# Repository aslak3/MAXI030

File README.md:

# MAXI030: a MC68030 based expandable computer

## Features as currently implemented

The specification for MAXI030, a [MC68030](https://www.nxp.com/docs/en/reference-manual/MC68030UM.pdf) based computer, is as follows:

* A core "glue" that is wired to [master](https://en.wikipedia.org/wiki/Bus_mastering) the 32 bit busses
* Glue is provided by an [EPF10K130EQC240-1](https://www.micro-semiconductor.com/datasheet/12-EPF10K100EFC256-2AA.pdf) FPGA
* A 68030 coupled with a [68882](https://www.nxp.com/docs/en/data-sheet/BR509.pdf)
* 512K x 16 flashes in the form of 2 x [SST39SF040](http://ww1.microchip.com/downloads/en/DeviceDoc/20005022C.pdf) in PLCC32
* 2 x [72 pin SIMM](https://en.wikipedia.org/wiki/SIMM#72-pin_SIMMs) slots with a controller implemented in the FPGA
* A [SC26C94](https://pdf.dzsc.com/6C9/SC26C94.pdf) QUART with the following arrangements of the four serial ports:
  * Two on RJ45 at RS-232 levels following the standard Cisco pinnout
  * One for [my Amiga 600 keyboard](https://www.aslak.net/index.php/amiga-600-avr-based-keyboard-controller/) on an RJ11
  * And a TTL header for debug and the bring-up
* Onboard 10Mbit/s Ethernet using a [RTL8019AS](http://www.ethernut.de/pdf/8019asds.pdf)
* A [PS/2](https://en.wikipedia.org/wiki/PS/2_port) port for keyboard and mouse using a splitter cable
* Four 16 bit wide by 16 MByte deep expansion slots compatible with cards like my [video card](https://www.aslak.net/index.php/2021/07/08/the-design-of-a-video-and-sound-card-for-midi020/) which was implemented for my earlier MC68020 board
* I2C bus with:
  * [DS13057](https://datasheets.maximintegrated.com/en/ds/DS1307.pdf) RTC
  * [LM75A](https://www.nxp.com/docs/en/data-sheet/LM75A.pdf) temperature sensor
  * [PCA9544APW](https://www.nxp.com/docs/en/data-sheet/PCA9544A.pdf) four way expansion slot bus multiplexer allowing expansion cards to attach to the I2C bus
* [IDE](https://en.wikipedia.org/wiki/Parallel_ATA) with DMA signals routed to the FPGA, though they are currently not utilised
* A [P7805-2000-S](https://www.mouser.co.uk/datasheet/2/670/p78_2000_s-1729053.pdf) 2A 5V potted switching regulator attached to a barrel jack

A [schematic](MAXI030.pdf) is included here, along with the [KiCAD](https://www.kicad.org) data files. Note that schematic symbols are included in the library cache. Whilst these boards were designed with KiCAD 4, the files in this repository are all KiCAD 6 format.

## PCB design

The PCB is a 4 layer board. The requirements to make the board are quite heavy; 6 mil traces are used, with 6.5 mil clearances between them. 3 traces pass between 100mil spaced pins in multiple places. My boards were manufactured by [JLCPCB](https://www.jlcpcb.com) with no issues.

## Glue logic core

A major feature of this board is the EPF10K130EQC240 FPGA. This component is part of Altera's [Flex 10KE](https://www.micro-semiconductor.com/datasheet/12-EPF10K100EFC256-2AA.pdf) family, which is a 3.3V/2.5V part descended from the [Flex 10K](https://www.dexsilicium.com/altera_flex_epf10k.pdf) line of 5V parts. These FPGAs are unfortunately obsolete, and difficult to get hold of; I sourced mine from [UTSource](https://www.utsource.net).

The board uses mixed 3.3V and 5V signaling. The Flex 10KE series is "special" in that it is fully 5V tolerant without an inline resistor, unlike later Altera parts such as the early Cylcones which are 5V tolerant but need an inline resistor. The Flex 10KE also have outputs compatible with 5V TTL levels. My previous projects have made heavy use of the 5V Flex 10K parts, but I have found that as the board frequency has increased, these FPGAs have reached their limit. Consequently this board switched to the Flex 10KE, despite the complexities inherent in a mixed signal level board.

Beside getting hold of the actual part a challenge facing anyone building this board is obtaining a compatible Altera Quartus version since Intel have, in their wisdom, removed from their site the 9.0sp2 version; the last that supported the Flex 10K(E) series. It can still be obtained if you know where to look, however.

Another small annoyance, related to the FPGA side of the board, is that two EPC2 configuration flashes are needed since this is a large, for the time, FPGA.

I have implemented the following functionality, all in VHDL:

* Core glue, address decoding etc
* A basic DRAM controller for one of the SIMM slots
* Buzzer and LED driver
* Simplistic interrupt routing (autovectored only for now)
* An I2C master to operate the RTC and temperature sensor
* A PS/2 controller for both PS/2 connections
* An SPI output channel, and bi-directional UART, both for debugging

The code for this functionality resides in the [MAXI030Core directory](MAXI030Core), where a more detailed description of the files used can be found.

As this is FPGA hardware, many other things could be implemented. In particular, the FPGA is wired to the full 32 bits of address and data, so a bus-mastering DMA controller could be constructed. This could be used for disk transfers, amongst other things, which would greatly speed up these operations. The interrupt handling is also basic at present, and vectored interrupts should probably be used.

It's worth pointing out, for completeness, that since the FPGA is attached to a 32 bit wide by 4GB address space it would theoretically be possible to use this board to replace the 68030 with some other custom softcore processor running inside the FPGA, with the 68030 disabled or simply not present. Perhaps a more interesting opportunity would be to implement a custom 68020+ style co-processor.

## Expansion Cards

The following three cards have been created:

1. [TestSRAM](ExpansionCards/TestSRAM/) - This is card is only really useful for the bringup. It has two 512KB SRAMs attached, along with pin headers attached to he expansion bus. It allows the system to be used without having a SIMM attached (and working).
2. [Printer+Sticks](ExpansionCards/Printer%2BSticks/) - This is a fairly simple card featuring a [MC68230](http://www.ceipsa.com/datasheet/MC68230.pdf) and some latches. The board does not feature a DB25 connector, instead the printer must be attached through a "standard" 2x13 PC style adapter. The latches are attached to DB9 Atari-style joystick ports.
3. [Video+Sound](ExpansionCards/Video%2BSound/) - The most interesting card by far; this a VGA card implemented with a Cyclone II FPGA and some fast 16 bit SRAM to hold the video framebuffer. Also featured is an I2S DAC.

The TestxSRAM card (such as it is) has been shown to be error-free. The Printer+Joystick card has been exercised by attaching an old 9 pin dot matrix printer and printing text, though this was with the earlier MIDI020 68020 board. The Video+Sound board has been attached to MAXI030 and, though it has a few teaming troubles, it appears to work well. The sound portion of that card has not been explored at all however.

More documentation on these cards will be forthcoming. For now, each expansion card directory contains the schematic and PCB files in KiCAD format, plus a PDF of the schematic, the BOM, and the rendered gerbers used to produce the cards.

## Machine-code monitor

Over the years I've extended my monitor to run on each 68K based board as I've produced them. The monitor is basic, but serviceable. It is in no way designed for software development; it's main purpose is to exercise the hardware. It has low-level (memory/IO operations) and high level functionality:

* IDE identify, read and write sectors
* PS/2 reading/writing
* I2C reading/writing
* And others

It is also used to start the Linux kernel.

The monitor source is held in its [own repository](https://www.github.com/aslak3/m68k-monitor).

## Linux

A Linux port has been started and seems to work quite well. The following hardware has been shown to work, by making very small changes to existing drivers or creating new ones:

* /dev/ttySC{0,1} UART ports - these map to Port A and Port B on the board
* IDE - though neither interrupt mode or DMA is currently supported so it is rather slow
* Ethernet - works well, though the transfers are on an 8 bit port
* RTC and temperature sensor - an I2C bus driver has been produced which can talk to these peripherals
* PS/2 - the driver implemented supports both ports
* Framebuffer - a very slow and Work in Progress driver for the video card I've built

With a 32MHz can installed, a modern Linux kernel will boot in about 2.5 minutes. But see the Gotchas section below.

A [fork of the Linux kernel](https://www.github.com/aslak3/linux.git) from early 2022 has work done at the head of the lm/maxi030 branch with the changes I've made.

The userland I'm currently using is based on a very old Debian build, even though the kernel is almost the latest, since running the latest 68k Debian packages results in a very slow system. This is another thing to investigate.

A script, which is a total hack, for generating an directory tree of Debian Linux is available in the [linux](linux) directory. This script can generate both sid (current) and sarge (old) Debian images. It must be edited before use to set the DNS resolver, interface addressing, passwords, custom packages and other things. It makes use of [multistrap](https://wiki.debian.org/Multistrap) and [QEUMU's 68K support](https://wiki.qemu.org/Documentation/Platforms/m68k) to do its thing.

As it currently stands, the Linux system is useable across the UART (via a login getty), and via the network. Both SSH and telnet are available, SSH being extremely slow as predicted. Console access, using the PS/2 port and my bitmap video card, is very much a work in progress, though I did have X running (very, very slowly) at one point.

The general process to get Linux running on MAXI030 is as follows, assuming the board is up and running with the monitor available via a UART port:

1. At present the MAC address of the Linux host, which will supply the image, is hardcoded into the monitor program in ne2k.c in the ne2k_transmit subroutine; change it to your PCs MAC address. Note that the MAXI030 MAC address is hardcoded to 11:22:33:44:55:66
2. Build a suitably patched kernel and convert it to a raw image
3. Modify the eth-sender program as required, at a minimum the device name for the connected ethernet interface is hardcoded
4. Run up the eth-sender program (it requires root), the kernel should be available in the same directory and called vmlinux.bin
5. Partition a Compact Flash: two partitions using MBR, partition 1 for swap and 2 for the rootfs in ext3 (ext4 will work with a newer Debian userland)
6. Modify the make-multistrap script as required
7. Create the Debian directory structure and copy it into partition two on the Compact Flash
8. Create a swap partition (mkswap) on partition one
9. Plug in the Compact Flash and turn on MAXI030
10. Transfer the kernel to MAXI030 with the linuxdl command
11. Run the kernel with a monitor command like: linuxrun "console=ttySC0,38400 root=/dev/sda2"
12. Wait for kernel to boot
13. Login via the getty, test the network etc

## Issues

The big issue I'm currently working on is board speed. With all the functionality enabled in the FPGA design, I'm currently not able to run the board at the maximum speed of the 68030 I have installed, 40MHz. Insteaed I must settle for running the board at 32MHz. In particular adding the FIFOs on the PS/2 controller results in an inoperable system at 40MHz. The FIFOs seem to be required when running in Linux since the kernel disables interrupts in some situations, which results in data loss.

The board also has a few very minor problems:

* The switching regulator footprint matches the 1A [SR10S05](https://www.xppower.com/portals/0/pdfs/SF_SR.pdf) and similar; the original 2A part fits but must hang off the board since its pinout is reversed. In use and with the video card inserted and a single SIMM attached I've rarely seen the current draw pass 500mA so I think a 1A regulator will be fine
* The silk screen labels for UART Port A and Port B are the wrong way around
* The labels for Enable/Disable on the MMU/cache jumpers are also backwards

## Blog

The best place to learn about this board is undoubtably [my blog](https://www.aslak.net/index.php/category/68k/), including these posts:

* [The design of MAXI030](https://www.aslak.net/index.php/2021/10/02/the-design-of-a-68030-based-expandable-computer/)
* [Porting Linux to the MAXI030](https://www.aslak.net/index.php/2022/01/11/porting-linux-to-the-68030-based-maxi030/)

I've also made a [short YouTube video](https://www.youtube.com/watch?v=WL3ttsiriho), which discusses the board and demos the Linux port.

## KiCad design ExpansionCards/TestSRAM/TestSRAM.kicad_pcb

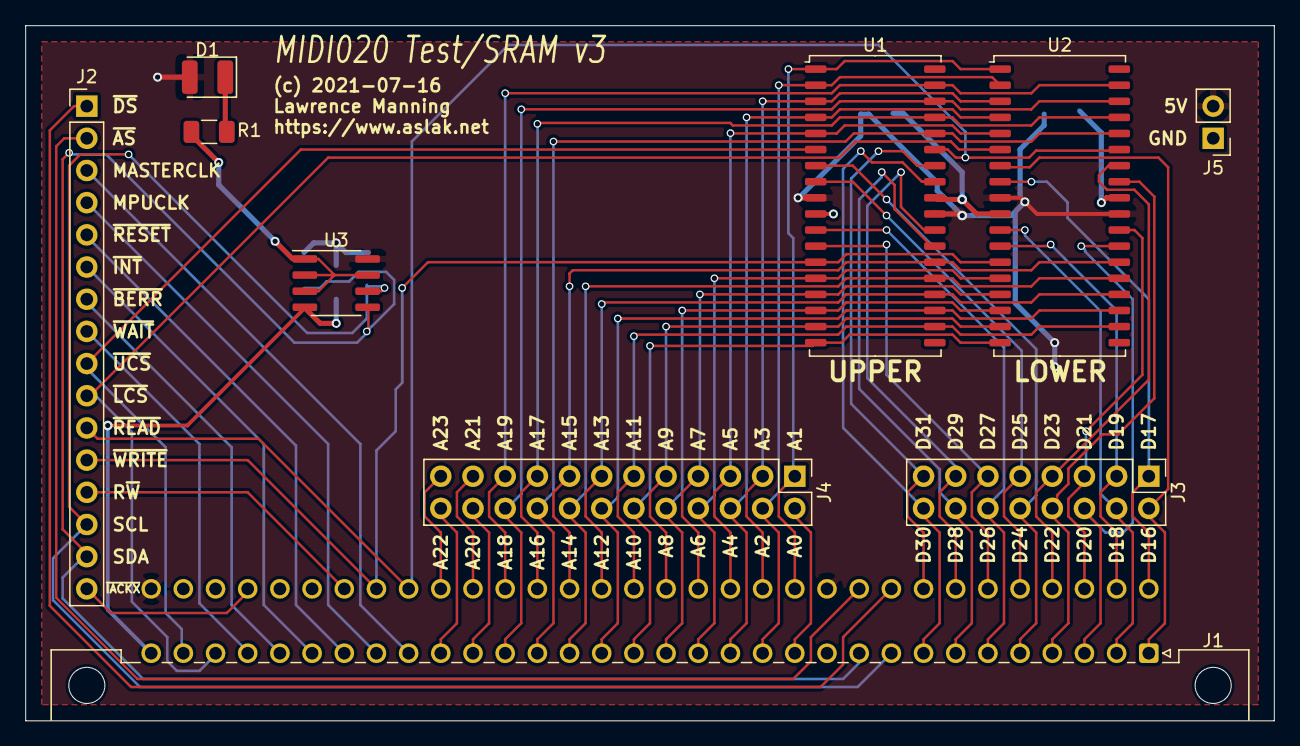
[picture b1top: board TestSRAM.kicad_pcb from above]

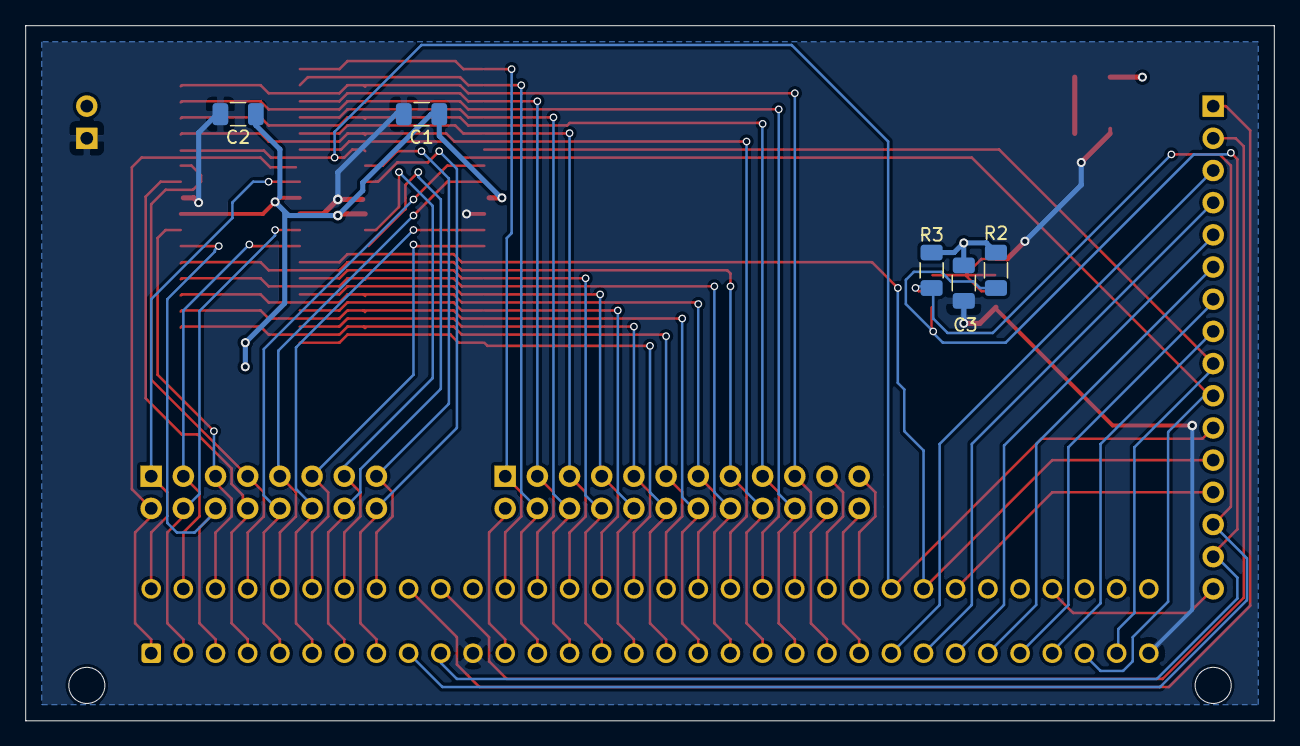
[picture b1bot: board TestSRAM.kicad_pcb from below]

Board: 2 copper layers, 98.6 x 54.9 mm, 15 parts (5 on the bottom side), 59 nets.

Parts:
C1, C2, C3: 0.1u; C_1206_3216Metric
D1: LED; LED_1210_3225Metric
J1: DIN_41612_3x32_MIDI020_CARD; DIN41612_C_2x32_Male_Horizontal_THT
J2: Conn_01x16; PinHeader_1x16_P2.54mm_Vertical
J3: Conn_02x08_Odd_Even; PinHeader_2x08_P2.54mm_Vertical
J4: Conn_02x12_Odd_Even; PinHeader_2x12_P2.54mm_Vertical
J5: Conn_01x02; PinHeader_1x02_P2.54mm_Vertical
R1: 1K; R_1206_3216Metric
R2, R3: 4.7K; R_1206_3216Metric
U1, U2: IS61C5128AL-10KLI; SOJ-36_10.16x23.49mm_P1.27mm
U3: AT24CS64-SSHM; SOIC-8_3.9x4.9mm_P1.27mm

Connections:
+5VD: C1.1, C2.1, C3.1, D1.2, J1.c11, J1.c32, J5.2, R2.1, R3.1, U1.9, U1.27, U2.9, U2.27, U3.8
/A0: J1.a12, J4.2
/A1: J1.c12, J4.1, U1.1, U2.1
/A2: J1.a13, J4.4, U1.2, U2.2
/A3: J1.c13, J4.3, U1.3, U2.3
/A4: J1.a14, J4.6, U1.4, U2.4
/A5: J1.c14, J4.5, U1.5, U2.5
/A6: J1.a15, J4.8, U1.14, U2.14
/A7: J1.c15, J4.7, U1.15, U2.15
/A8: J1.a16, J4.10, U1.16, U2.16
/A9: J1.c16, J4.9, U1.17, U2.17
/A10: J1.a17, J4.12, U1.18, U2.18
/A11: J1.c17, J4.11, U1.20, U2.20
/A12: J1.a18, J4.14, U1.21, U2.21
/A13: J1.c18, J4.13, U1.22, U2.22
/A14: J1.a19, J4.16, U1.23, U2.23
/A15: J1.c19, J4.15, U1.24, U2.24
/A16: J1.a20, J4.18, U1.32, U2.32
/A17: J1.c20, J4.17, U1.33, U2.33
/A18: J1.a21, J4.20, U1.34, U2.34
/A19: J1.c21, J4.19, U1.35, U2.35
/A20: J1.a22, J4.22
/A21: J1.c22, J4.21
/A22: J1.a23, J4.24
/A23: J1.c23, J4.23
/D16: J1.a1, J3.2, U2.7
/D17: J1.c1, J3.1, U2.8
/D18: J1.a2, J3.4, U2.11
/D19: J1.c2, J3.3, U2.12
/D20: J1.a3, J3.6, U2.25
/D21: J1.c3, J3.5, U2.26
/D22: J1.a4, J3.8, U2.29
/D23: J1.c4, J3.7, U2.30
/D24: J1.a5, J3.10, U1.7
/D25: J1.c5, J3.9, U1.8
/D26: J1.a6, J3.12, U1.11
/D27: J1.c6, J3.11, U1.12
/D28: J1.a7, J3.14, U1.25
/D29: J1.c7, J3.13, U1.26
/D30: J1.a8, J3.16, U1.29
/D31: J1.c8, J3.15, U1.30
GNDD: C1.2, C2.2, C3.2, J1.a11, J1.a32, J5.1, R1.1, U1.10, U1.28, U2.10, U2.28, U3.1, U3.2, U3.3, U3.4, U3.7
MASTERCLK: J1.a24, J2.3
MPUCLK: J1.a25, J2.4
unnamed: D1.1, R1.2
R~W: J1.c26, J2.13
SCL: J1.a9, J2.14, R3.2, U3.6
SDA: J1.a10, J2.15, R2.2, U3.5
~AS: J1.c10, J2.2
~BERR: J1.a28, J2.7
~DS: J1.c9, J2.1
~IACKX: J1.c29, J2.16
~INT: J1.a27, J2.6
~LCS: J1.a30, J2.10, U2.6
~READ: J1.c24, J2.11, U1.31, U2.31
~RESET: J1.a26, J2.5
~UCS: J1.a31, J2.9, U1.6
~WAIT: J1.a29, J2.8
~WRITE: J1.c25, J2.12, U1.13, U2.13

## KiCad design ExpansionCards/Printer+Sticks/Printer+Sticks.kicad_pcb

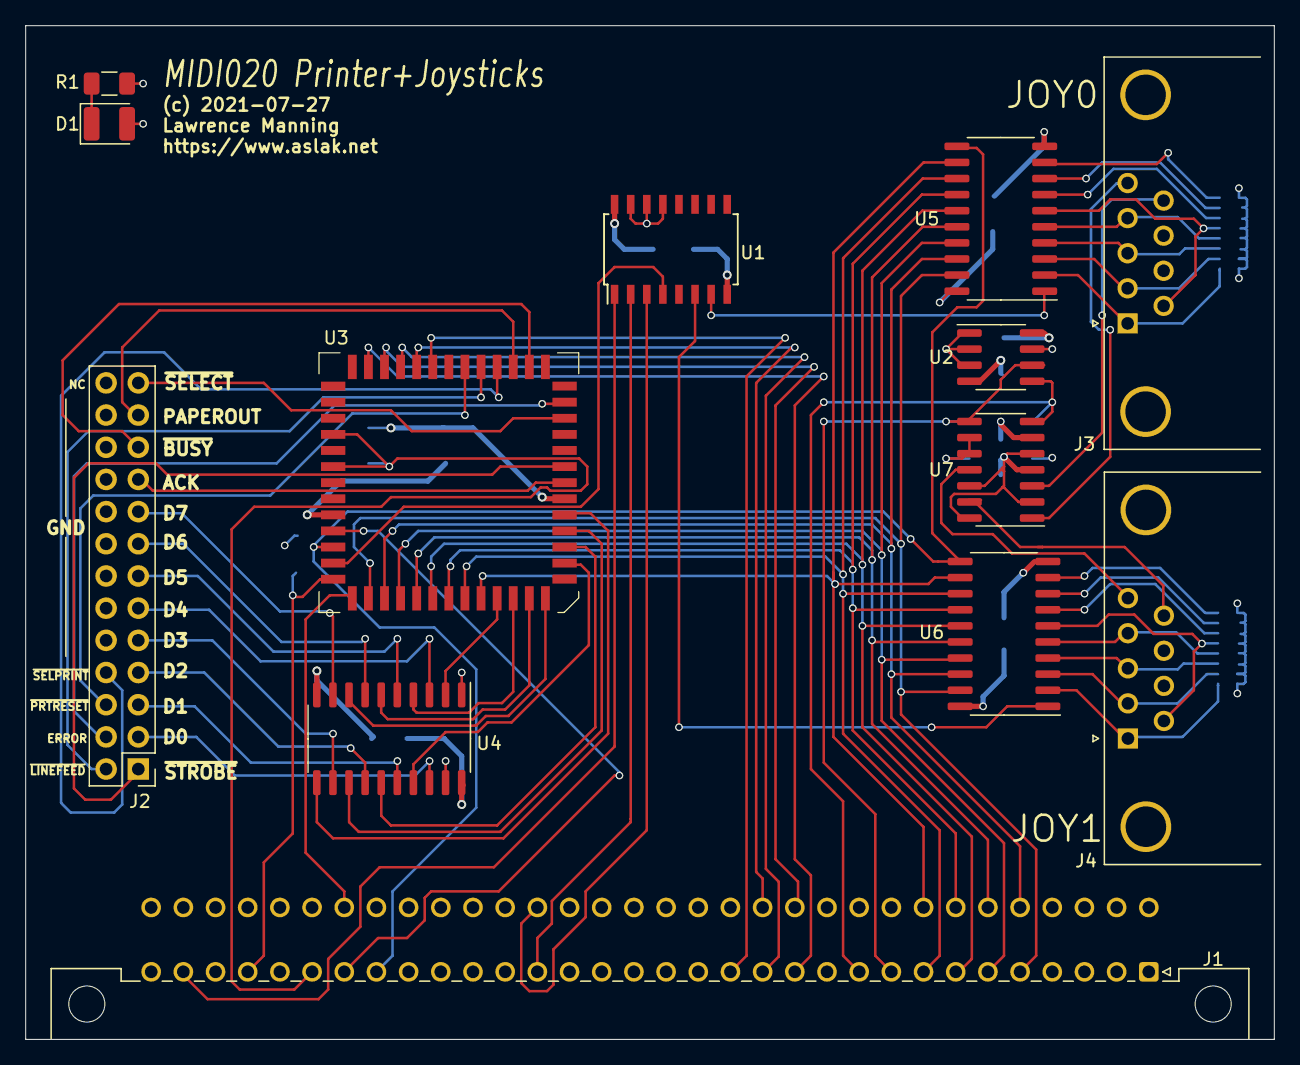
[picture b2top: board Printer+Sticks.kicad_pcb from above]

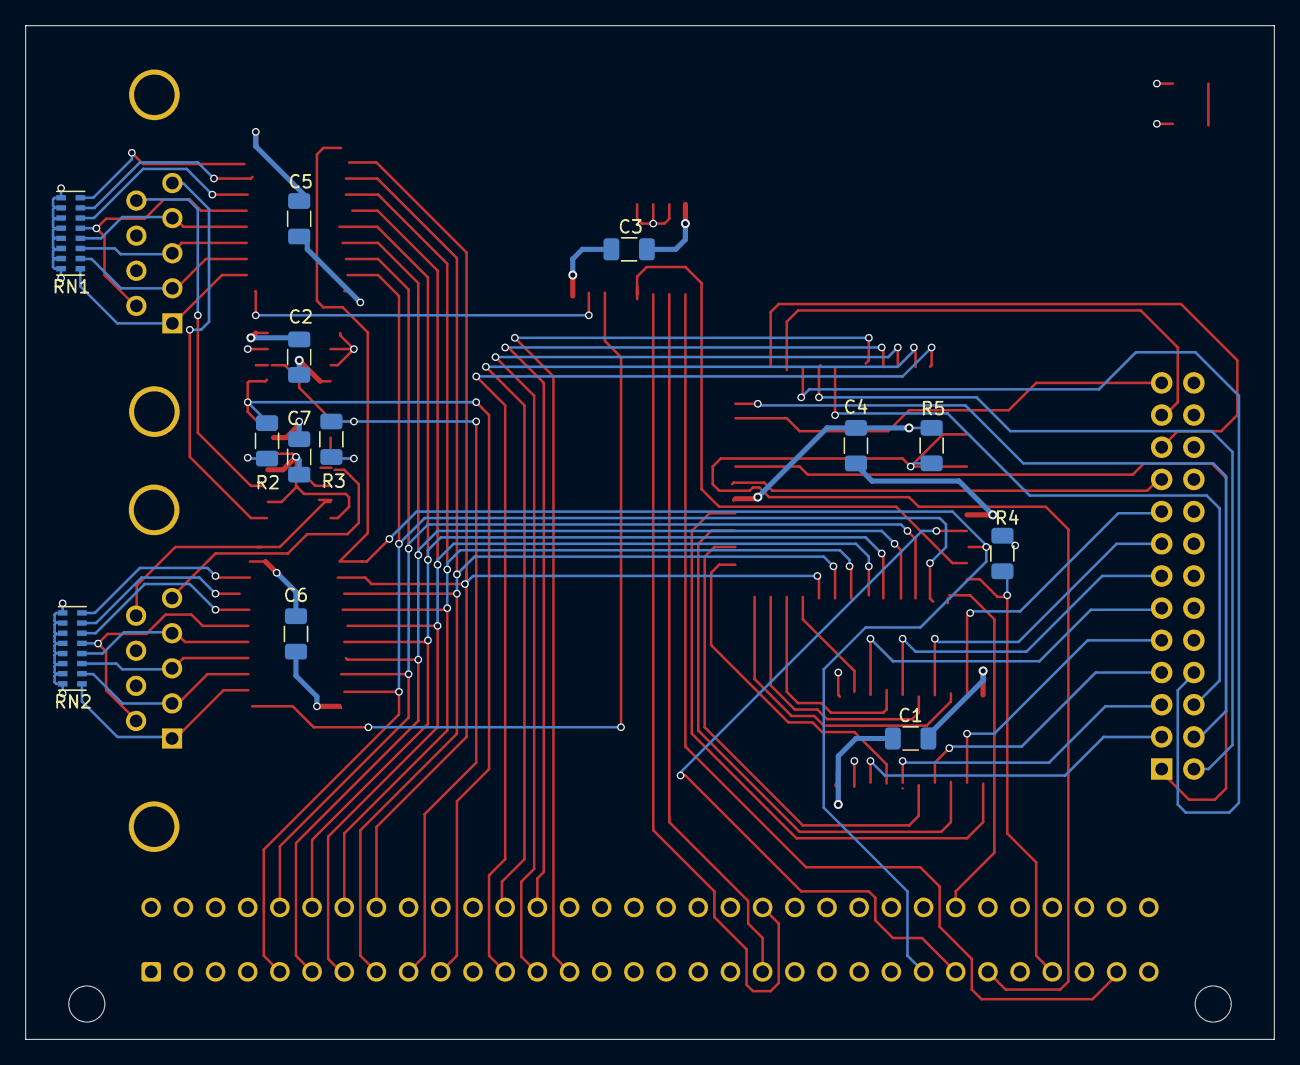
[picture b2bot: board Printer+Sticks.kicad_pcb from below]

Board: 4 copper layers, 98.6 x 80.0 mm, 26 parts (13 on the bottom side), 74 nets.

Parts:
C1, C2, C3, C4, C5, C6, C7: 0.1u; C_1206_3216Metric
D1: LED; LED_1210_3225Metric
J1: DIN_41612_3x32_MIDI020_CARD; DIN41612_C_2x32_Male_Horizontal_THT
J2: Conn_02x13_Odd_Even; PinHeader_2x13_P2.54mm_Vertical
J3, J4: DB9_Male_MountingHoles; DSUB-9_Male_Horizontal_P2.77x2.84mm_EdgePinOffset7.70mm_Hou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
R1: 1K; R_1206_3216Metric
R2, R3, R4, R5: 4.7K; R_1206_3216Metric
RN1, RN2: 10K; R_Cat16-8
U1: 74LS139; SOIC-16W_5.3x10.2mm_P1.27mm
U2: AT24CS64-SSHM; SOIC-8_3.9x4.9mm_P1.27mm
U3: MC68230; PLCC-52
U4: 74HC244; SO-20_5.3x12.6mm_P1.27mm
U5, U6: 74LS574; SO-20_5.3x12.6mm_P1.27mm
U7: MCP3428; SOIC-14_3.9x8.7mm_P1.27mm

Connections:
+5VD: C1.1, C2.1, C3.1, C4.1, C5.1, C6.1, C7.1, D1.2, J1.c11, J1.c32, J3.7, J4.7, R2.1, R3.1, R4.1, R5.1, RN1.9, RN1.10, RN1.11, RN1.12, RN1.13, RN1.14, RN1.15, RN1.16, RN2.9, RN2.10, RN2.11, RN2.12, RN2.13, RN2.14, RN2.15, RN2.16, U1.13, U1.14, U1.15, U1.16, U2.8, U3.13, U4.20, U5.20, U6.20, U7.6, U7.9, U7.10
/Printer/ACK: J2.19, U3.14
/Printer/ERROR: J2.4, U3.19
/Printer/PA0: U3.4, U4.2
/Printer/PA1: U3.5, U4.4
/Printer/PA2: U3.6, U4.6
/Printer/PA3: U3.7, U4.8
/Printer/PA4: U3.9, U4.17
/Printer/PA5: U3.10, U4.15
/Printer/PA6: U3.11, U4.13
/Printer/PA7: U3.12, U4.11
/Printer/PAPEROUT: J2.23, U3.23
/Printer/PRTD0: J2.3, U4.18
/Printer/PRTD1: J2.5, U4.16
/Printer/PRTD2: J2.7, U4.14
/Printer/PRTD3: J2.9, U4.12
/Printer/PRTD4: J2.11, U4.3
/Printer/PRTD5: J2.13, U4.5
/Printer/PRTD6: J2.15, U4.7
/Printer/PRTD7: J2.17, U4.9
/Printer/~BUSY: J2.21, U3.22
/Printer/~LINEFEED: J2.2, U3.25
/Printer/~PRTRESET: J2.6, U3.26
/Printer/~SELECTPRINTER: J2.8, U3.24
/Printer/~SELECT: J2.25, U3.18
/Printer/~STROBE: J2.1, U3.15
A0: J1.a12, U3.32
A1: J1.c12, U3.31
A2: J1.a13, U3.30
A3: J1.c13, U3.29
A4: J1.a14, U3.28
A16: J1.a20, U1.2
A17: J1.c20, U1.3
D24: J1.a5, U3.48, U5.19, U6.19
D25: J1.c5, U3.49, U5.18, U6.18
D26: J1.a6, U3.50, U5.17, U6.17
D27: J1.c6, U3.51, U5.16, U6.16
D28: J1.a7, U3.52, U5.15, U6.15
D29: J1.c7, U3.1, U5.14, U6.14
D30: J1.a8, U3.2, U5.13, U6.13
D31: J1.c8, U3.3, U5.12, U6.12
GNDD: C1.2, C2.2, C3.2, C4.2, C5.2, C6.2, C7.2, J1.a11, J1.a32, J2.10, J2.12, J2.14, J2.16, J2.18, J2.20, J2.22, J2.24, J3.0, J3.8, J4.0, J4.8, R1.1, U1.8, U2.1, U2.2, U2.3, U2.4, U2.7, U3.42, U4.1, U4.10, U4.19, U5.10, U6.10, U7.2, U7.4, U7.5, U7.12, U7.14
JOY0XPOT: J3.5, U7.1
JOY0YPOT: J3.9, U7.3
JOY1XPOT: J4.5, U7.11
JOY1YPOT: J4.9, U7.13
MPUCLK: J1.a25, U3.44, U5.11, U6.11
unnamed: D1.1, R1.2
unnamed: RN1.6, U5.7
unnamed: RN1.7, U5.8
unnamed: RN1.8, U5.9
unnamed: RN2.6, U6.7
unnamed: RN2.7, U6.8
unnamed: RN2.8, U6.9
R~W: J1.c26, U3.47
SCL: J1.a9, R3.2, U2.6, U7.8
SDA: J1.a10, R2.2, U2.5, U7.7
~INT: J1.a27, R5.2, U3.37, U3.39
~JOY0CS: U1.7, U5.1
~JOY0DOWN: J3.2, RN1.2, U5.3
~JOY0FIRE: J3.6, RN1.5, U5.6
~JOY0LEFT: J3.3, RN1.3, U5.4
~JOY0RIGHT: J3.4, RN1.4, U5.5
~JOY0UP: J3.1, RN1.1, U5.2
~JOY1CS: U1.6, U6.1
~JOY1DOWN: J4.2, RN2.2, U6.3
~JOY1FIRE: J4.6, RN2.5, U6.6
~JOY1LEFT: J4.3, RN2.3, U6.4
~JOY1RIGHT: J4.4, RN2.4, U6.5
~JOY1UP: J4.1, RN2.1, U6.2
~PITCS: U1.4, U3.45
~RESET: J1.a26, U3.43
~UCS: J1.a31, U1.1
~WAIT: J1.a29, R4.2, U3.46

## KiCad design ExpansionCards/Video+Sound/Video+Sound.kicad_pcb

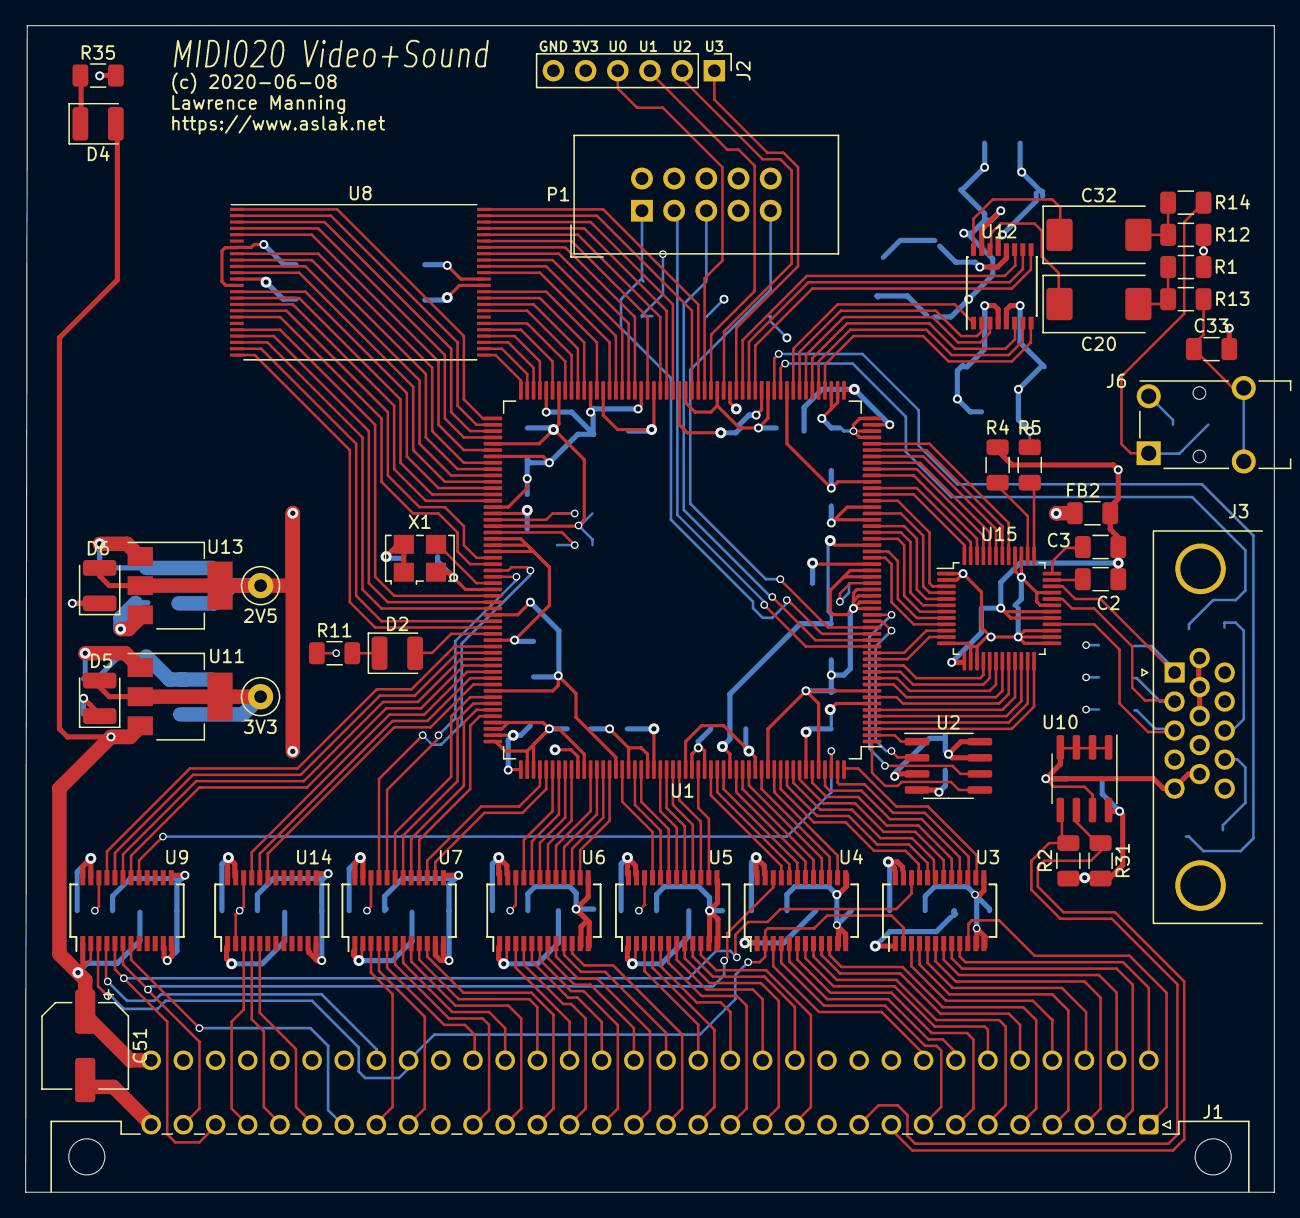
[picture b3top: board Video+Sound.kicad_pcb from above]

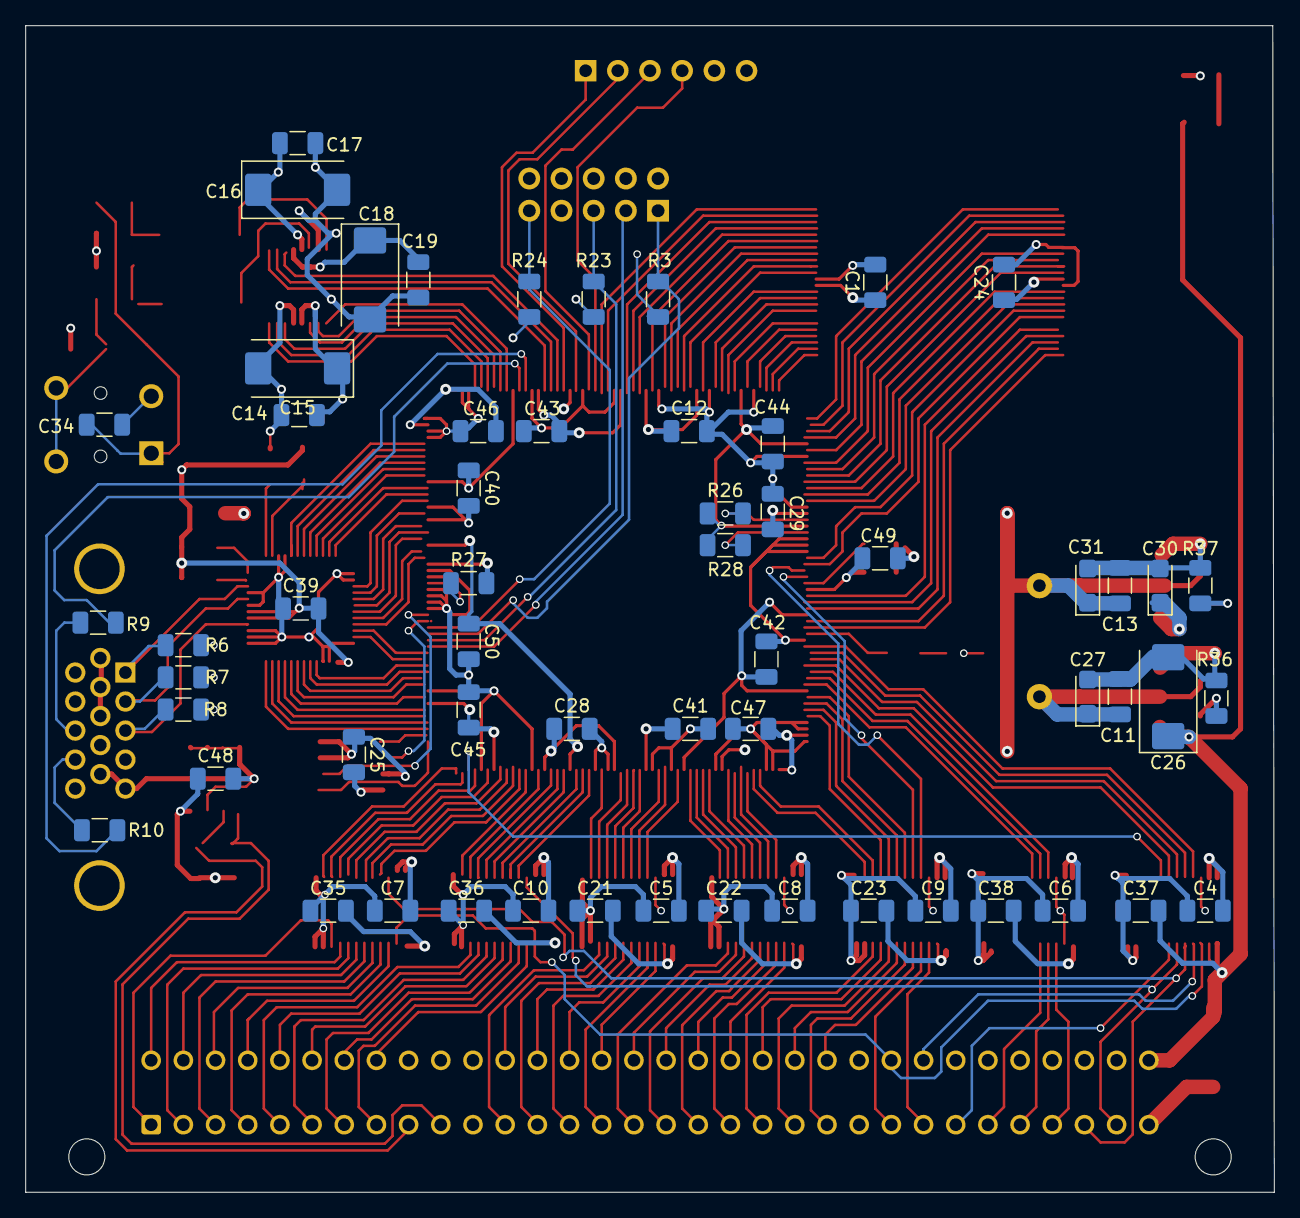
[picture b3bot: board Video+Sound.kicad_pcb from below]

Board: 4 copper layers, 98.6 x 92.1 mm, 102 parts (58 on the bottom side), 217 nets.

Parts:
C1, C2, C3, C4, C5, C6, C7, C8, C9, C10, C11, C12, C13, C14, C17, C19, C21, C22, C23, C24, C25, C28, C35, C36, C37, C38, C39, C41, C42, C43, C44, C45, C46, C47, C48, C49, C50: 0.1u; C_1206_3216Metric
C15, C16, C18, C20, C26, C32: 47u; CP_EIA-7343-15_Kemet-W
C27, C30, C31: 10u; CP_EIA-3216-10_Kemet-I
C29, C40: 1n; C_1206_3216Metric
C33, C34: 10n; C_1206_3216Metric
C51: 220u; CP_Elec_6.3x7.7
D2, D4, D5, D6: LED; LED_1210_3225Metric
FB2: Bead; L_1206_3216Metric
J1: DIN_41612_3x32_MIDI020_CARD; DIN41612_C_2x32_Male_Horizontal_THT
J2: Conn_01x06; PinHeader_1x06_P2.54mm_Vertical
J3: DB15HD_FEMALE_SVGA; DSUB-15-HD_Female_Horizontal_P2.29x1.98mm_EdgePinOffset3.03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
J6: STEREO_AUDIOJACK; Jack_3.5mm_Switronic_ST-005-G_horizontal
P1: CONN_02X05_JTAG; IDC-Header_2x05_P2.54mm_Vertical
R1, R12: 220K; R_1206_3216Metric
R2, R5, R31: 4.7K; R_1206_3216Metric
R3, R11, R23, R24, R35, R36, R37: 1K; R_1206_3216Metric
R4: 530; R_1206_3216Metric
R6, R7, R8: 75; R_1206_3216Metric
R9, R10: 47; R_1206_3216Metric
R13, R14: 100; R_1206_3216Metric
R26, R27, R28: 10K; R_1206_3216Metric
TP9: 3V3; TestPoint_Loop_D1.80mm_Drill1.0mm_Beaded
TP11: 2V5; TestPoint_Loop_D1.80mm_Drill1.0mm_Beaded
U1: EP2C8Q208I8N; PQFP-208_28x28mm_P0.5mm
U2: EPCQnA; SOIC-8_3.9x4.9mm_P1.27mm
U3, U4, U5, U6, U7, U9, U14: SN74LVC8T245; SSOP-24_3.9x8.7mm_P0.635mm
U8: IS61WV102416BLL-10TLI; TSOP-I-48_18.4x12mm_P0.5mm
U10: AT24CS64-SSHM; SOIC-8_3.9x4.9mm_P1.27mm
U11: AZ1117-3.3; SOT-223-3_TabPin2
U12: UDA1334ATS; SSOP-16_4.4x5.2mm_P0.65mm
U13: AZ1117-1.2; SOT-223-3_TabPin2
U15: ADV7123KSTZ140; LQFP-48_7x7mm_P0.5mm
X1: MASTEROSC; Oscillator_SMD_SeikoEpson_SG8002LB-4Pin_5.0x3.2mm

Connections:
+1V2: C13.1, C29.1, C31.1, C41.1, C43.1, C46.1, C47.1, C50.1, D6.2, TP11.1, U1.32, U1.51, U1.53, U1.66, U1.79, U1.120, U1.155, U1.157, U1.178, U1.190, U13.2
+3.3VDAC: C2.2, C3.2, C16.1, C17.1, C39.1, FB2.1, R5.1, U12.13, U15.13, U15.29, U15.30
+3V3: C1.1, C4.1, C5.1, C6.1, C7.1, C8.1, C9.1, C10.1, C11.1, C12.1, C14.1, C15.1, C24.1, C25.1, C27.1, C28.1, C30.1, C40.1, C42.1, C44.1, C45.1, C49.1, D5.2, FB2.2, J2.5, P1.4, R23.1, R24.1, R26.1, R27.1, R28.1, TP9.1, U1.7, U1.29, U1.42, U1.62, U1.71, U1.83, U1.91, U1.98, U1.109, U1.122, U1.136, U1.148, U1.166, U1.172, U1.183, U1.194, U1.202, U2.3, U2.7, U2.8, U3.23, U3.24, U4.23, U4.24, U5.23, U5.24, U6.23, U6.24, U7.23, U7.24, U8.12, U8.36, U9.23, U9.24, U11.2, U12.4, U13.3, U14.23, U14.24, X1.1, X1.4
+5VD: C21.1, C22.1, C23.1, C26.1, C35.1, C36.1, C37.1, C38.1, C48.1, C51.1, D4.2, J1.c11, J1.c32, R2.1, R31.1, U3.1, U4.1, U5.1, U5.2, U6.1, U6.2, U7.1, U7.2, U9.1, U9.2, U10.8, U11.3, U14.1
/FPGA/USER0: J2.4, U1.75
/FPGA/USER1: J2.3, U1.74
/FPGA/USER2: J2.2, U1.72
/FPGA/USER3: J2.1, U1.70
/Sound/VOUTL: C20.1, U12.14
/Sound/VOUTR: C32.1, U12.16
/Sound/VREF: C18.1, C19.1, U12.12
A0: J1.a12, U5.10
A1: J1.c12, U5.9
A2: J1.a13, U5.8
A3: J1.c13, U5.7
A4: J1.a14, U5.6
A5: J1.c14, U5.5
A6: J1.a15, U5.4
A7: J1.c15, U5.3
A8: J1.a16, U6.10
A9: J1.c16, U6.9
A10: J1.a17, U6.8
A11: J1.c17, U6.7
A12: J1.a18, U6.6
A13: J1.c18, U6.5
A14: J1.a19, U6.4
A15: J1.c19, U6.3
A16: J1.a20, U7.10
A17: J1.c20, U7.9
A18: J1.a21, U7.8
A19: J1.c21, U7.7
A20: J1.a22, U7.6
A21: J1.c22, U7.5
BLUE: J3.3, R8.1, U15.28
BLUE0: U1.13, U15.16
BLUE1: U1.12, U15.17
BLUE2: U1.11, U15.18
BLUE3: U1.10, U15.19
BLUE4: U1.8, U15.20
BLUE5: U1.6, U15.21
BLUE6: U1.5, U15.22
BLUE7: U1.4, U15.23
CFGASDI: U1.1, U2.5
CFGDATA: U1.20, U2.2
CFGDCLK: U1.21, U2.6
D16: J1.a1, U3.10
D17: J1.c1, U3.9
D18: J1.a2, U3.8
D19: J1.c2, U3.7
D20: J1.a3, U3.6
D21: J1.c3, U3.5
D22: J1.a4, U3.4
D23: J1.c4, U3.3
D24: J1.a5, U4.10
D25: J1.c5, U4.9
D26: J1.a6, U4.8
D27: J1.c6, U4.7
D28: J1.a7, U4.6
D29: J1.c7, U4.5
D30: J1.a8, U4.4
D31: J1.c8, U4.3
DACCLK: U1.3, U15.24
GNDA: C1.2, C4.2, C5.2, C6.2, C7.2, C8.2, C9.2, C10.2, C11.2, C12.2, C13.2, C14.2, C15.2, C16.2, C17.2, C18.2, C19.2, C21.2, C22.2, C23.2, C24.2, C25.2, C26.2, C27.2, C28.2, C29.2, C30.2, C31.2, C33.2, C34.2, C35.2, C36.2, C37.2, C38.2, C39.2, C40.2, C41.2, C42.2, C43.2, C44.2, C45.2, C46.2, C47.2, C48.2, C49.2, C50.2, C51.2, J1.a11, J1.a32, J2.6, J3.0, J3.5, J3.6, J3.7, J3.8, J3.10, J6.S, P1.2, P1.10, R1.2, R3.2, R4.2, R6.2, R7.2, R8.2, R11.2, R12.2, R35.2, R36.2, R37.2, U1.9, U1.22, U1.23, U1.24, U1.25, U1.27, U1.28, U1.36, U1.38, U1.49, U1.50, U1.52, U1.54, U1.55, U1.65, U1.73, U1.78, U1.85, U1.93, U1.100, U1.111, U1.119, U1.124, U1.125, U1.126, U1.132, U1.140, U1.153, U1.154, U1.156, U1.158, U1.159, U1.167, U1.174, U1.177, U1.184, U1.186, U1.196, U1.204, U2.4, U3.11, U3.12, U3.13, U4.11, U4.12, U4.13, U5.11, U5.12, U5.13, U5.22, U6.11, U6.12, U6.13, U6.22, U7.11, U7.12, U7.13, U7.22, U8.7, U8.13, U8.37, U9.11, U9.12, U9.13, U9.22, U10.1, U10.2, U10.3, U10.4, U10.7, U11.1, U12.5, U12.15, U13.1, U14.2, U14.11, U14.12, U14.13, U14.22, U15.1, U15.2, U15.12, U15.14, U15.15, U15.25, U15.26, U15.27, U15.31, U15.33, U15.39, U15.40, X1.2
GREEN: J3.2, R7.1, U15.32
GREEN0: U1.39, U15.3
GREEN1: U1.37, U15.4
GREEN2: U1.35, U15.5
GREEN3: U1.34, U15.6
GREEN4: U1.33, U15.7
GREEN5: U1.31, U15.8
GREEN6: U1.30, U15.9
GREEN7: U1.15, U15.10
HSYNC: R9.1, U1.63
I2SBCLK: U1.61, U12.1
I2SDATAI: U1.59, U12.3
I2SDEEMCLKOUT: U1.67, U12.9
I2SMUTE: U1.56, U12.8
I2SPLL0: U1.68, U12.10
I2SSFOR0: U1.69, U12.11
I2SSFOR1: U1.57, U12.7
I2SSYSCLKPLL1: U1.58, U12.6
I2SWS: U1.60, U12.2
LA0: U1.185, U5.14
LA1: U1.182, U5.15
LA2: U1.181, U5.16
LA3: U1.180, U5.17
LA4: U1.179, U5.18
LA5: U1.176, U5.19
LA6: U1.175, U5.20
LA7: U1.173, U5.21
LA8: U1.171, U6.14
LA9: U1.170, U6.15
LA10: U1.169, U6.16
LA11: U1.168, U6.17
LA12: U1.165, U6.18
LA13: U1.164, U6.19
LA14: U1.163, U6.20
LA15: U1.162, U6.21
LA16: U1.161, U7.14
LA17: U1.160, U7.15
LA18: U1.152, U7.16
LA19: U1.151, U7.17
LA20: U1.150, U7.18
LA21: U1.149, U7.19
LD16: U1.208, U3.14
LD17: U1.207, U3.15
LD18: U1.205, U3.16
LD19: U1.203, U3.17
LD20: U1.201, U3.18
LD21: U1.200, U3.19
LD22: U1.199, U3.20
LD23: U1.198, U3.21
LD24: U1.197, U4.14
LD25: U1.195, U4.15
LD26: U1.193, U4.16
LD27: U1.192, U4.17
LD28: U1.191, U4.18
LD29: U1.189, U4.19
LD30: U1.188, U4.20
LD31: U1.187, U4.21
LMASTERCLK: U1.130, U7.20
LMPUCLK: U1.129, U7.21
MASTERCLK: J1.a24, U7.4
MPUCLK: J1.a25, U7.3
unnamed: C2.1, U15.35
unnamed: C3.1, U15.36
unnamed: C20.2, R1.1, R13.1
unnamed: C32.2, R12.1, R14.1
unnamed: C33.1, J6.T, R13.2
unnamed: C34.1, J6.R, R14.2
unnamed: D2.1, R11.1
unnamed: D4.1, R35.1
unnamed: D5.1, R36.1
unnamed: D6.1, R37.1
unnamed: J3.13, R9.2
unnamed: J3.14, R10.2
unnamed: R4.1, U15.37
unnamed: R5.2, U15.38
unnamed: R26.2, U1.121
unnamed: R27.2, U1.26
unnamed: R28.2, U1.123
RED: J3.1, R6.1, U15.34
RED0: U1.48, U15.41
RED1: U1.47, U15.42
RED2: U1.46, U15.43
RED3: U1.45, U15.44
RED4: U1.44, U15.45
RED5: U1.43, U15.46
RED6: U1.41, U15.47
RED7: U1.40, U15.48
SCL: J1.a9, R31.2, U10.6
SDA: J1.a10, R2.2, U10.5
TCK: P1.1, R3.1, U1.18
TDI: P1.9, R24.2, U1.19
TDO: P1.3, U1.16
TMS: P1.5, R23.2, U1.17
USERLED: D2.2, U1.139
VA0: U1.110, U8.5
VA1: U1.108, U8.4
VA2: U1.107, U8.3
VA3: U1.106, U8.2
VA4: U1.105, U8.1
VA5: U1.76, U8.48
VA6: U1.77, U8.47
VA7: U1.80, U8.46
VA8: U1.81, U8.45
VA9: U1.97, U8.30
VA10: U1.99, U8.29
VA11: U1.101, U8.28
VA12: U1.102, U8.27
VA13: U1.103, U8.26
VA14: U1.104, U8.25
VA15: U1.138, U8.24
VA16: U1.137, U8.23
VA17: U1.135, U8.22
VA18: U1.134, U8.21
VA19: U1.133, U8.20
VD0: U1.112, U8.8
VD1: U1.113, U8.9
VD2: U1.114, U8.10
VD3: U1.115, U8.11
VD4: U1.116, U8.14
VD5: U1.117, U8.15
VD6: U1.118, U8.16
VD7: U1.127, U8.17
VD8: U1.96, U8.32
VD9: U1.95, U8.33
VD10: U1.94, U8.34
VD11: U1.92, U8.35
VD12: U1.90, U8.38
VD13: U1.89, U8.39
VD14: U1.88, U8.40
VD15: U1.87, U8.41
VIDEOCLK: U1.131, X1.3
VSYNC: R10.1, U1.64
~BERR: J1.a28, U14.4
~CFGCS: U1.2, U2.1
~INT: J1.a27, U14.5
~LBERR: U1.146, U14.20
~LCS: J1.a30, U3.22, U9.5
~LINT: U1.147, U14.19
~LLCS: U1.143, U9.19
~LREAD: U1.141, U9.21
~LRESET: U1.206, U9.17
~LUCS: U1.144, U9.18
~LWAIT: U1.145, U14.21
~LWRITE: U1.142, U9.20
~READ: J1.c24, U3.2, U4.2, U9.3
~RESET: J1.a26, U9.7
~UCS: J1.a31, U4.22, U9.6
~VGABLANK: U1.14, U15.11
~VLCS: U1.86, U8.42
~VREAD: U1.82, U8.44
~VUCS: U1.84, U8.43
~VWRITE: U1.128, U8.18
~WAIT: J1.a29, U14.3
~WRITE: J1.c25, U9.4

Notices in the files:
ExpansionCards/Printer+Sticks/Printer+Sticks.kicad_pcb:
(c) 2021-07-27
ExpansionCards/TestSRAM/TestSRAM.kicad_pcb:
(c) 2021-07-16
ExpansionCards/Video+Sound/Video+Sound.kicad_pcb:
(c) 2020-06-08
spreadout.kicad_pcb:
(c) 2020-010-02
